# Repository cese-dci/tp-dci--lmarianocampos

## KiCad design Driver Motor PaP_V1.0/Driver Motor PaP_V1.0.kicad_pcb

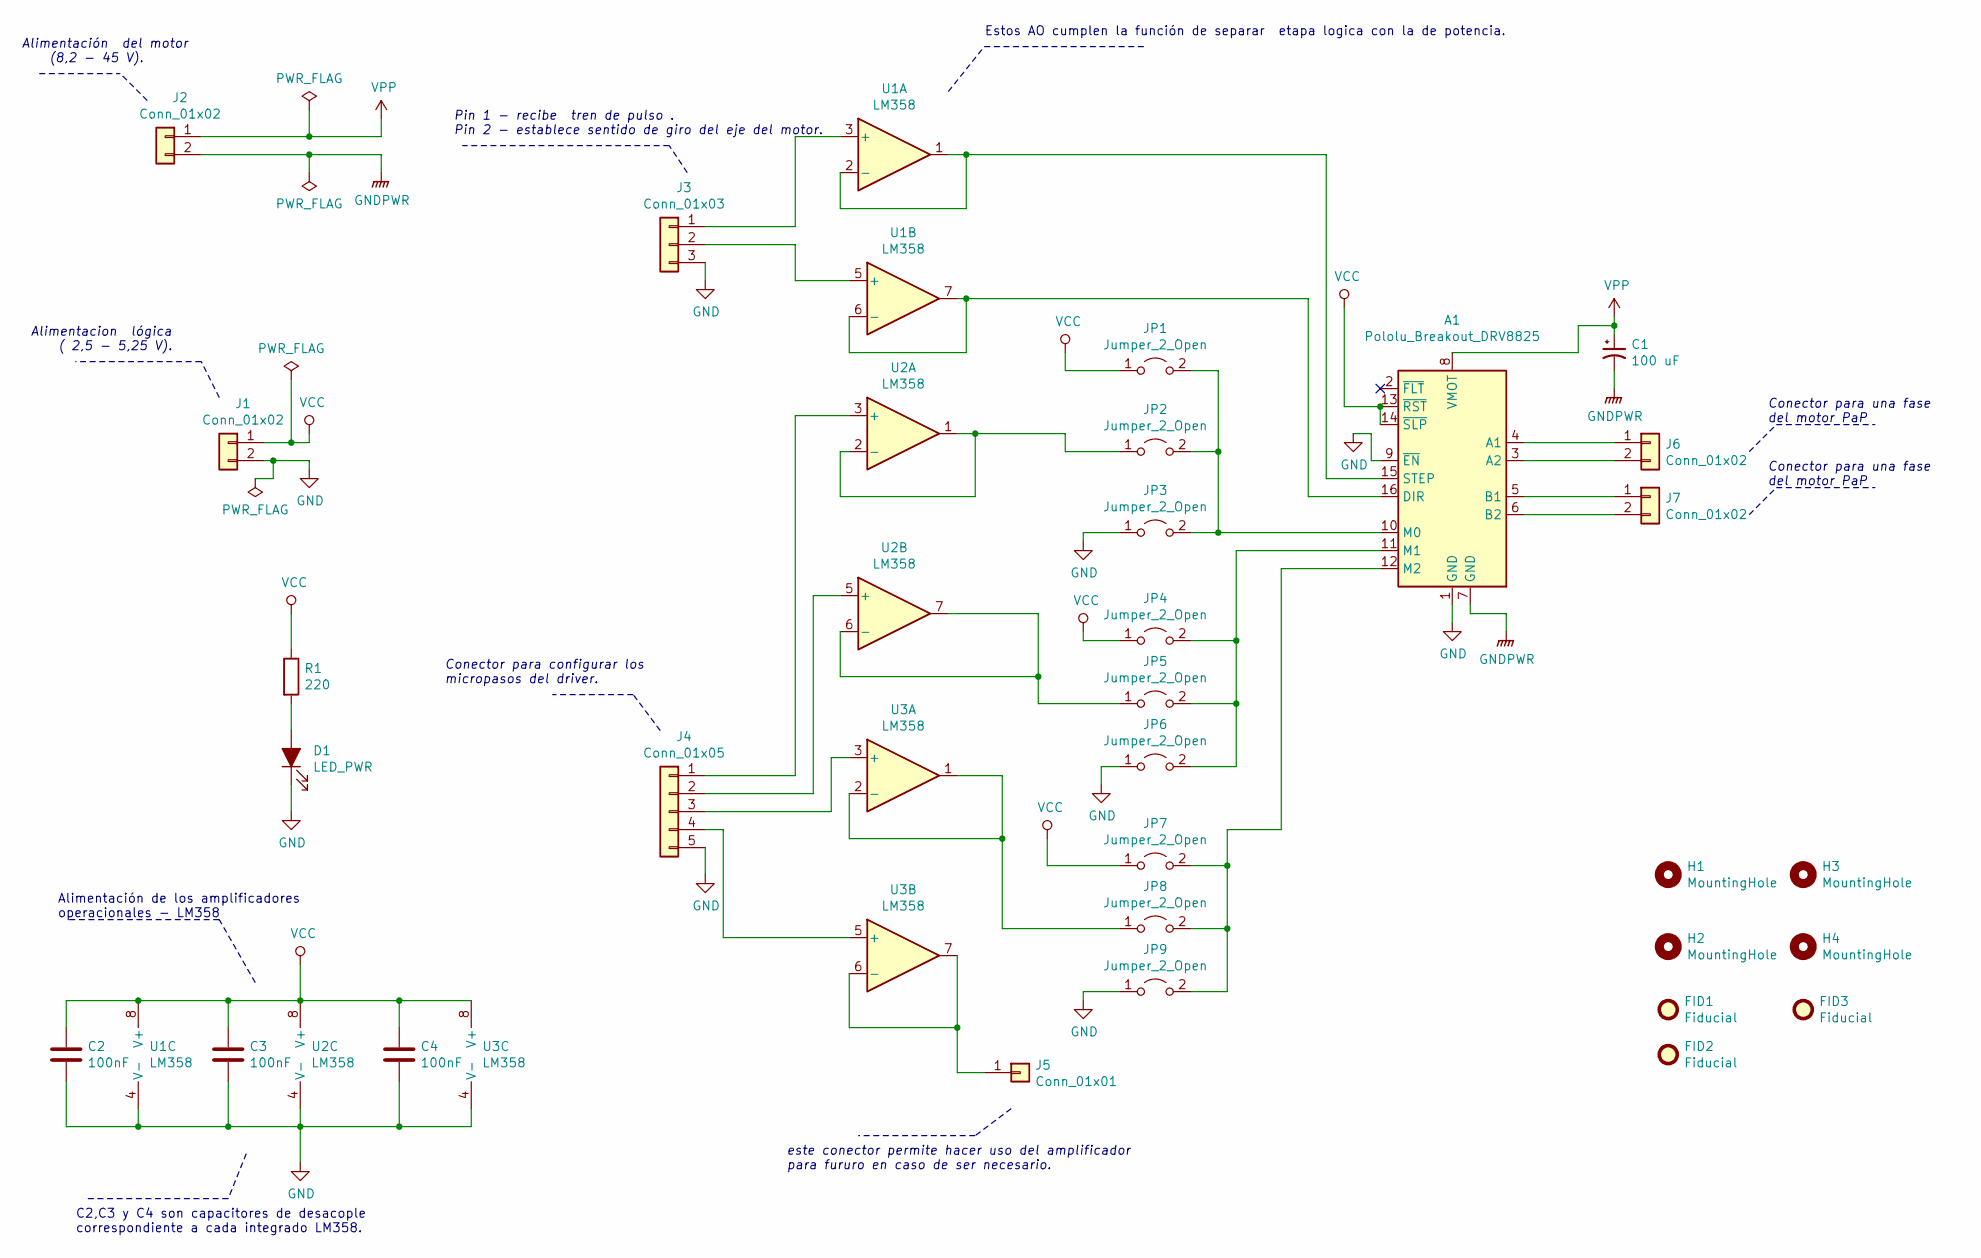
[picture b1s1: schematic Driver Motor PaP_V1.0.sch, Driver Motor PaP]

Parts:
A1: Pololu_Breakout_DRV8825; Pololu_Breakout-16_15.2x20.3mm; digi-key # 2183-2133-ND
C1: 100 uF; CP_Elec_6.3x5.4; digi-key # 493-226-1-ND
C2, C3, C4: 100nF; C_0805_2012Metric_Pad1.15x1.40mm_HandSolder; digi-key # 490-16313-2-ND
D1: LED_PWR; LED_0805_2012Metric_Pad1.15x1.40mm_HandSolder
FID1, FID2, FID3: Fiducial; Fiducial_1mm_Mask2mm
H1, H2, H3, H4: MountingHole; MountingHole_3.2mm_M3
J1, J2: Conn_01x02; TerminalBlock_Phoenix_MKDS-1,5-2-5.08_1x02_P5.08mm_Horizont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; digi-key # A113320-ND
J3: Conn_01x03; Molex_KK-254_AE-6410-03A_1x03_P2.54mm_Vertical; digi-key # WM411-ND
J4: Conn_01x05; Molex_KK-254_AE-6410-05A_1x05_P2.54mm_Vertical; digi-key # WM4114-ND
J5: Conn_01x01; PinHeader_1x01_P2.54mm_Vertical; digi-key # WM50014-01-ND
J6, J7: Conn_01x02; PinHeader_1x02_P2.54mm_Vertical; digi-key # WM8072-ND
JP1, JP2, JP3, JP4, JP5, JP6, JP7, JP8, JP9: Jumper_2_Open; PinHeader_1x02_P2.54mm_Vertical; digi-key # WM8072-ND
R1: 220; R_0805_2012Metric_Pad1.15x1.40mm_HandSolder
U1, U2, U3: LM358; SOIC-8_3.9x4.9mm_P1.27mm; digi-key # 497-1591-2-ND

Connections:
GND: A1.1 (GND), A1.9 (~EN), C2.2, C3.2, C4.2, D1.1 (K), J1.2, J3.3, J4.5, JP3.1 (A), JP6.1 (A), JP9.1 (A), U1.4 (V-), U2.4 (V-), U3.4 (V-)
GNDPWR: A1.7 (GND), C1.2, J2.2
unnamed: A1.3 (A2), J6.2
unnamed: A1.4 (A1), J6.1
unnamed: A1.5 (B1), J7.1
unnamed: A1.6 (B2), J7.2
unnamed: A1.10 (M0), JP1.2 (B), JP2.2 (B), JP3.2 (B)
unnamed: A1.11 (M1), JP4.2 (B), JP5.2 (B), JP6.2 (B)
unnamed: A1.12 (M2), JP7.2 (B), JP8.2 (B), JP9.2 (B)
unnamed: A1.15 (STEP), U1.1, U1.2 (-)
unnamed: A1.16 (DIR), U1.6 (-), U1.7
unnamed: D1.2 (A), R1.2
unnamed: J3.1, U1.3 (+)
unnamed: J3.2, U1.5 (+)
unnamed: J4.1, U2.3 (+)
unnamed: J4.2, U2.5 (+)
unnamed: J4.3, U3.3 (+)
unnamed: J4.4, U3.5 (+)
unnamed: J5.1, U3.6 (-), U3.7
unnamed: JP2.1 (A), U2.1, U2.2 (-)
unnamed: JP5.1 (A), U2.6 (-), U2.7
unnamed: JP8.1 (A), U3.1, U3.2 (-)
VCC: A1.13 (~RST), A1.14 (~SLP), C2.1, C3.1, C4.1, J1.1, JP1.1 (A), JP4.1 (A), JP7.1 (A), R1.1, U1.8 (V+), U2.8 (V+), U3.8 (V+)
VPP: A1.8 (VMOT), C1.1, J2.1

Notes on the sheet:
Conector para una fase del motor PaP
Conector para configurar los micropasos del driver.
Pin 1 - recibe tren de pulso . Pin 2 - establece sentido de giro del eje del motor.
Alimentación del motor (8,2 - 45 V).
Estos AO cumplen la función de separar etapa logica con la de potencia.
Alimentacion lógica ( 2,5 - 5,25 V).
Alimentación de los amplificadores operacionales - LM358
este conector permite hacer uso del amplificador para fururo en caso de ser necesario.
C2,C3 y C4 son capacitores de desacople correspondiente a cada integrado LM358.

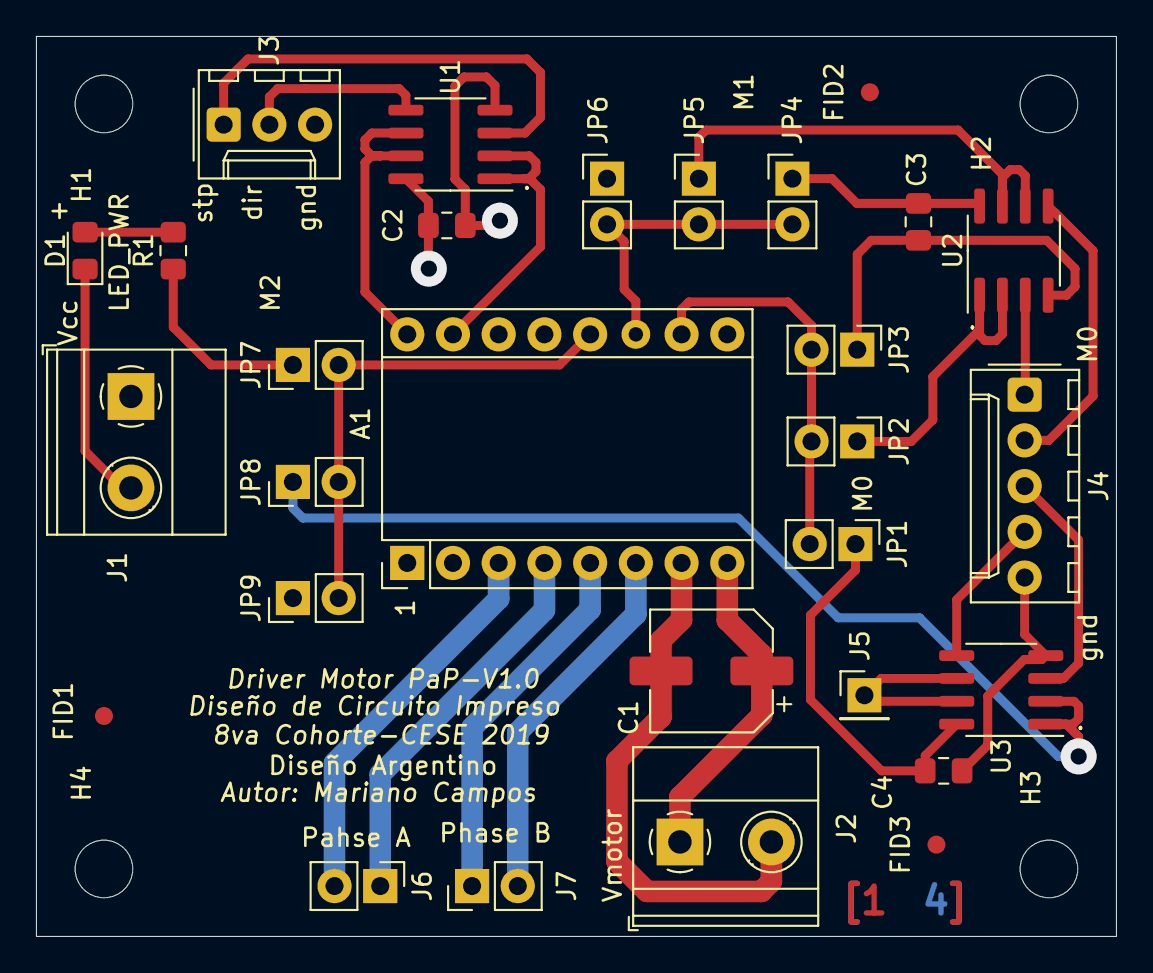
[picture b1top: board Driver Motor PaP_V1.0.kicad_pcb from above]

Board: 4 copper layers, 60.0 x 50.0 mm, 33 parts (0 on the bottom side), 24 nets.

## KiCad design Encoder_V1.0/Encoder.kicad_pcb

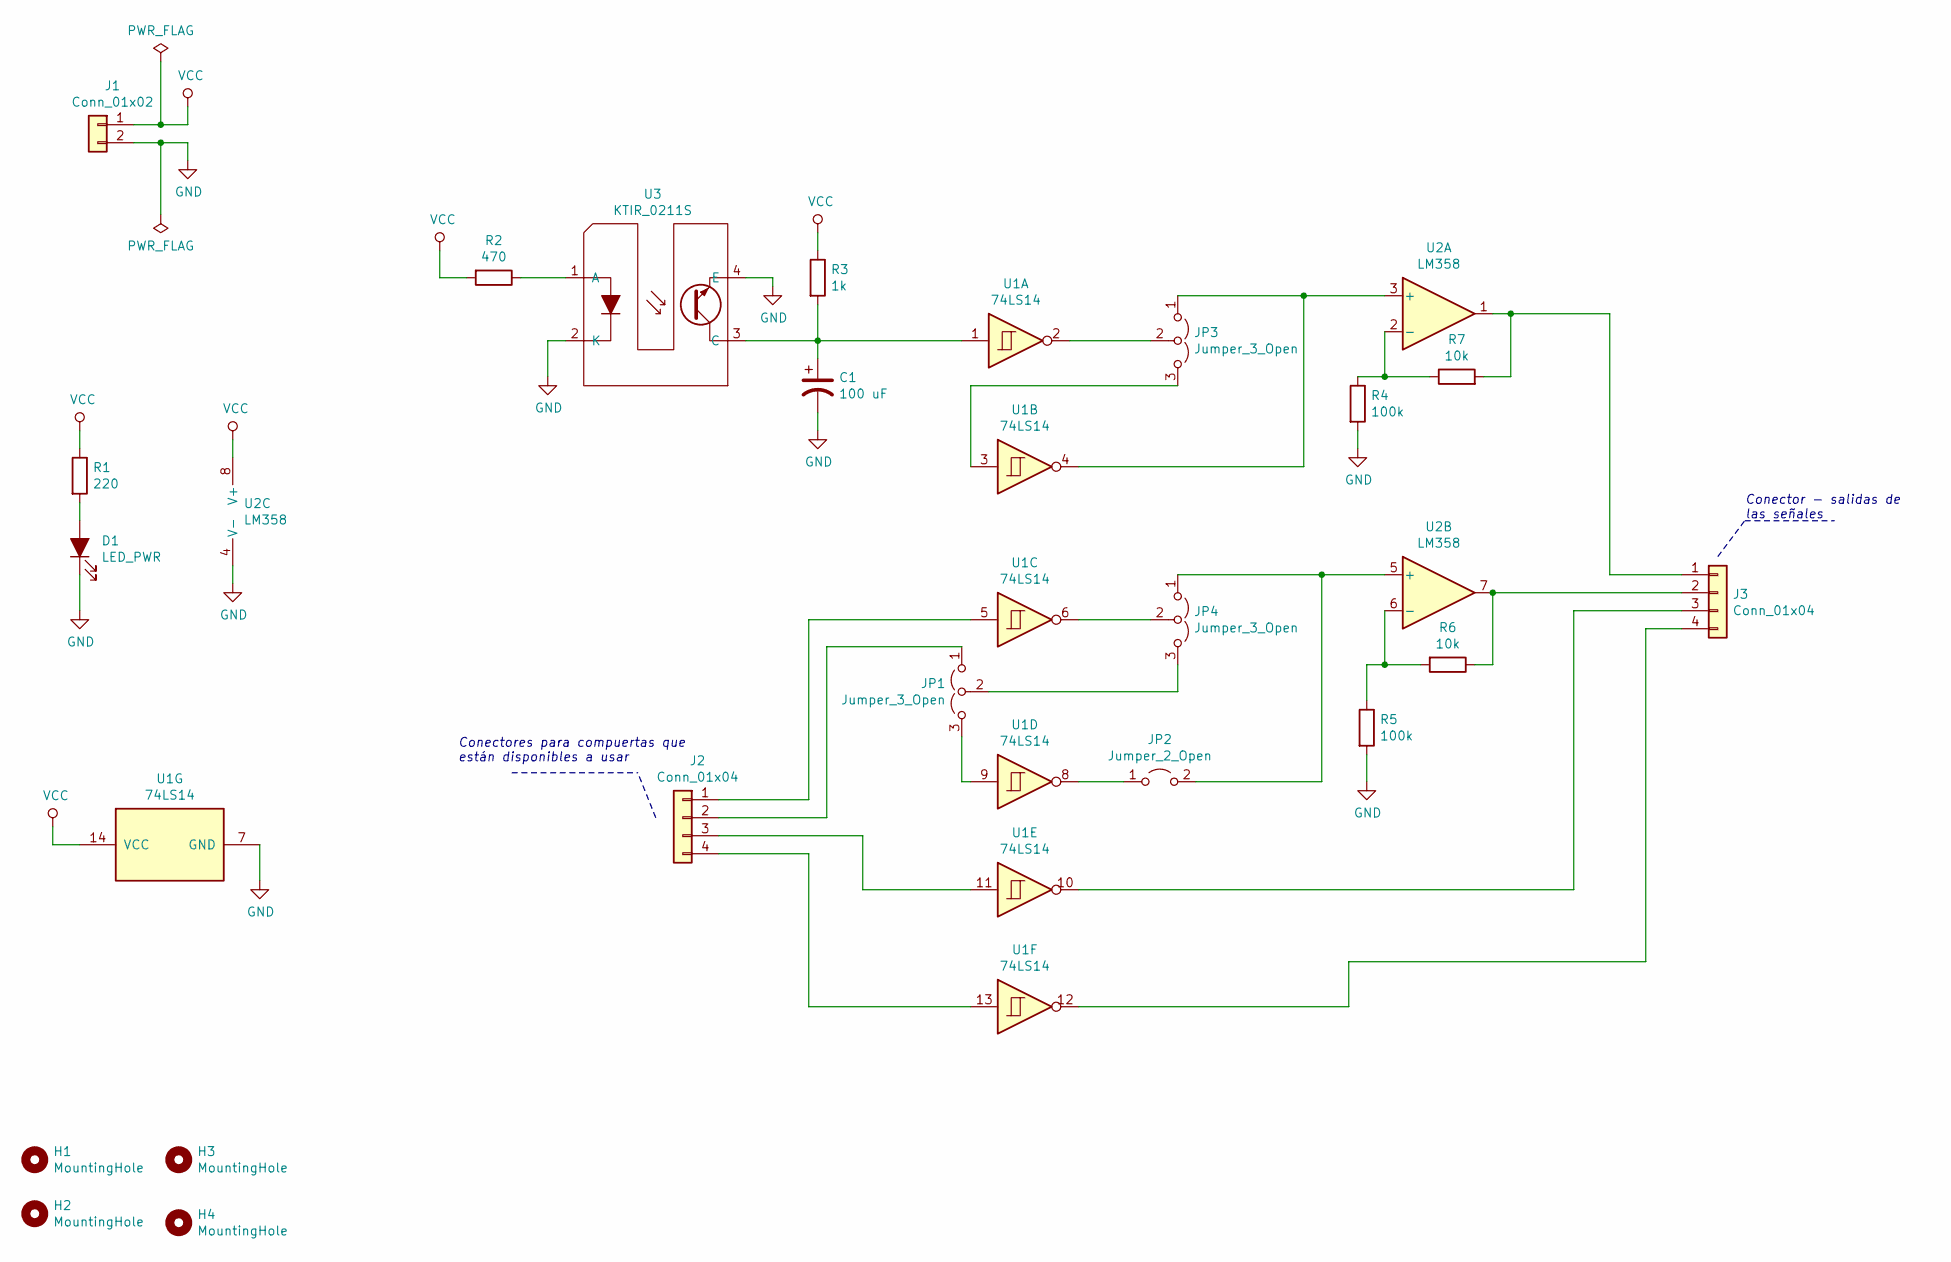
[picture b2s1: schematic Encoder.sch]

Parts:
C1: 100 uF; CP_Radial_D6.3mm_P2.50mm
D1: LED_PWR; LED_D3.0mm
H1, H2, H3, H4: MountingHole; MountingHole_3mm_Pad
J1: Conn_01x02; PinHeader_1x02_P2.54mm_Vertical
J2, J3: Conn_01x04; PinHeader_1x04_P2.54mm_Vertical
JP1, JP3, JP4: Jumper_3_Open; PinHeader_1x03_P2.54mm_Vertical
JP2: Jumper_2_Open; PinHeader_1x02_P2.54mm_Vertical
R1: 220; R_Axial_DIN0207_L6.3mm_D2.5mm_P10.16mm_Horizontal
R2: 470; R_Axial_DIN0207_L6.3mm_D2.5mm_P10.16mm_Horizontal
R3: 1k; R_Axial_DIN0207_L6.3mm_D2.5mm_P10.16mm_Horizontal
R4, R5: 100k; R_Axial_DIN0207_L6.3mm_D2.5mm_P10.16mm_Horizontal
R6, R7: 10k; R_Axial_DIN0207_L6.3mm_D2.5mm_P10.16mm_Horizontal
U1: 74LS14; DIP-14_W7.62mm
U2: LM358; DIP-8_W7.62mm
U3: KTIR_0211S

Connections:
GND: C1.2, D1.1 (K), J1.2, R4.2, R5.2, U1.7 (GND), U2.4 (V-), U3.2 (K), U3.4 (E)
unnamed: C1.1, R3.2, U1.1, U3.3 (C)
unnamed: D1.2 (A), R1.2
unnamed: J2.1, U1.5
unnamed: J2.2, JP1.1 (A)
unnamed: J2.3, U1.11
unnamed: J2.4, U1.13
unnamed: J3.1, R7.2, U2.1
unnamed: J3.2, R6.1, U2.7
unnamed: J3.3, U1.10
unnamed: J3.4, U1.12
unnamed: JP1.2 (C), JP4.3 (B)
unnamed: JP1.3 (B), U1.9
unnamed: JP2.1 (A), U1.8
unnamed: JP2.2 (B), JP4.1 (A), U2.5 (+)
unnamed: JP3.1 (A), U1.4, U2.3 (+)
unnamed: JP3.2 (C), U1.2
unnamed: JP3.3 (B), U1.3
unnamed: JP4.2 (C), U1.6
unnamed: R2.1, U3.1 (A)
unnamed: R4.1, R7.1, U2.2 (-)
unnamed: R5.1, R6.2, U2.6 (-)
VCC: J1.1, R1.1, R2.2, R3.1, U1.14 (VCC), U2.8 (V+)

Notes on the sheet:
Conectores para compuertas que están disponibles a usar
Conector - salidas de las señales

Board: 2 copper layers, 23 parts (0 on the bottom side), 23 nets, no tracks yet.

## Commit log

2019-10-04 my second commit
2019-10-10 Corrección que sugirio el revisador
2019-10-10 Corrección de las sugerencia del revisor 1.1
2019-10-30 PCB Driver Motor PaP
2019-10-31 correcciones driver motor PaP v1.0
2019-10-31 nuevas correcciones - errores drc
2019-10-31 Agregado:fabricante, pieza y biblioteca de footprint y componentes
2019-11-01 modelos 3D agregados
2019-11-05 modificación de margen y traslado de componentes a la capa superior
2019-11-05 corrección de serigrafía
2019-11-07 correción dehuellas delos terminales block y modelo 3D
2019-11-07 modificación en el ruteo
